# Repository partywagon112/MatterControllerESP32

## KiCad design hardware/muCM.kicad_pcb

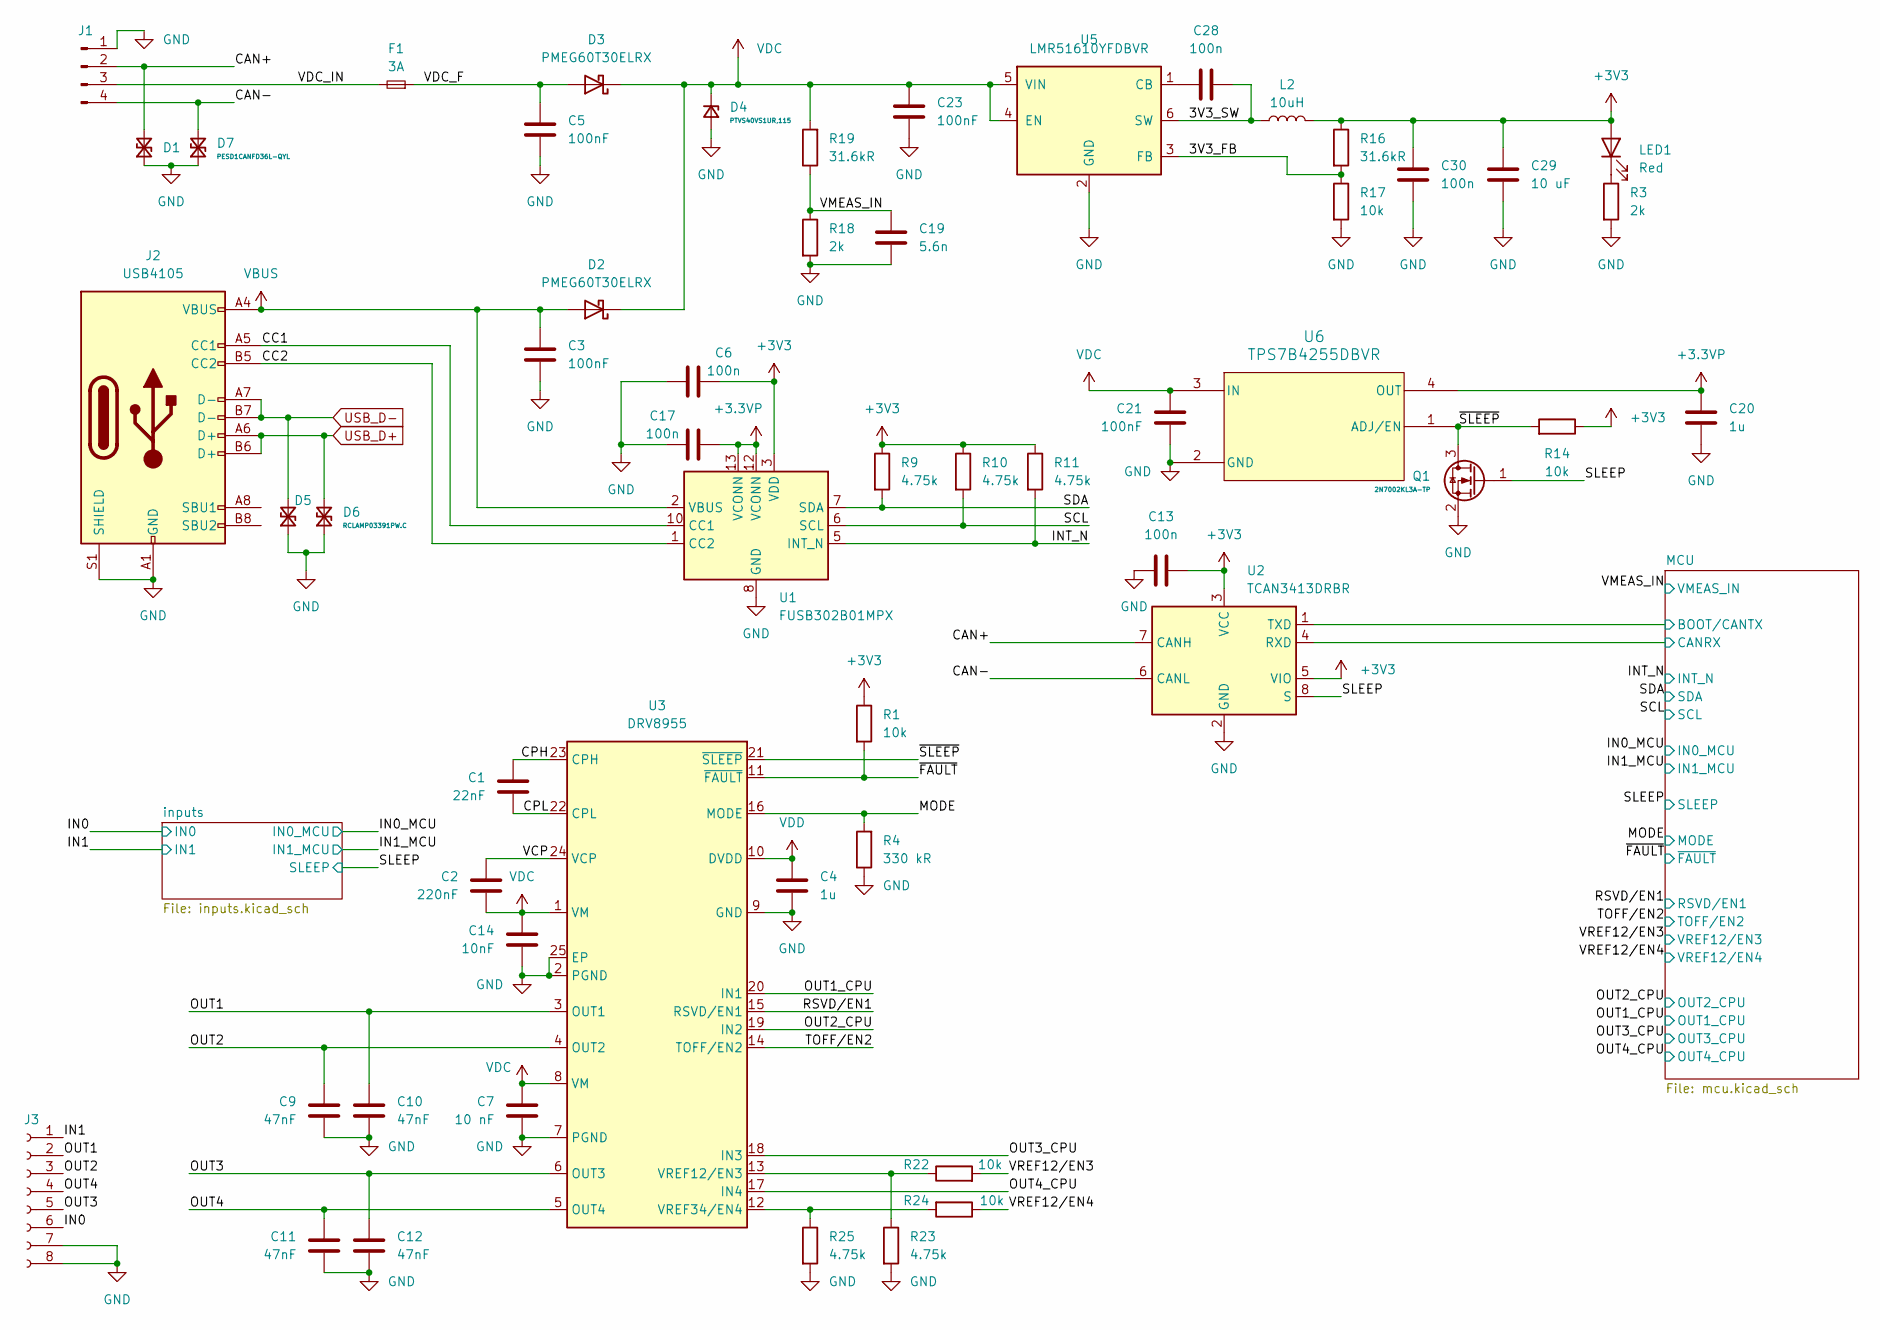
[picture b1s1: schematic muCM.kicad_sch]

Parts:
C1: 22nF; C_0603_1608Metric; MPN CL10B223KC8WPNC; DigiKey SPN 1276-CL10B223KC8WPNCCT-ND
C2: 220nF; C_0603_1608Metric; MPN HMK107C7224MAHTE; DigiKey SPN 587-5013-1-ND
C3, C5, C21, C23: 100nF; C_0603_1608Metric; MPN GCJ188R72A104KA01D; DigiKey SPN 490-13420-1-ND
C4, C20: 1u; C_0603_1608Metric; MPN GRT188R61H105KE13D; DigiKey SPN 490-12330-1-ND
C6, C13, C17, C28, C30: 100n; C_0402_1005Metric; MPN GCM155R71H104KE02J
C7: 10 nF; R_0603_1608Metric; MPN GCM188R71H103KA37D; DigiKey SPN 490-4778-1-ND
C9, C10, C11, C12: 47nF; C_0603_1608Metric; MPN CGA3E3X7S2A473K080AE; DigiKey SPN 445-173702-1-ND
C14: 10nF; C_0603_1608Metric; MPN CL10B103KC8WPNC; DigiKey SPN 1276-6556-1-ND
C19: 5.6n; C_0402_1005Metric; MPN GCM155R71H562KA55D; DigiKey SPN 490-GCM155R71H562KA55DCT-ND
C29: 10 uF; C_0603_1608Metric; MPN GRT188R61E106ME13D; DigiKey SPN 490-12323-1-ND
D1, D7: PESD1CANFD36L-QYL; D_SOD-882; MPN PESD1CANFD36L-QYL; DigiKey SPN 1727-PESD1CANFD36L-QYLCT-ND
D2, D3: PMEG60T30ELRX; Nexperia_CFP3_SOD-123W; MPN PMEG60T30ELRX; DigiKey SPN 1727-7806-1-ND
D4: PTVS40VS1UR,115; Nexperia_CFP3_SOD-123W; MPN PTVS40VS1UR,115; DigiKey SPN 1727-5873-1-ND
D5, D6: RCLAMP03391PW.C; D_SOD-882; MPN RCLAMP03391PW.C; DigiKey SPN 600-RCLAMP03391PW.CCT-ND
F1: 3A; Fuse_0805_2012Metric; MPN MFU0805FF03000P100; DigiKey SPN MFU08053.00CT-ND
J1: CDM806-04A-MP-F011-67; CUI_CDM806-04A-MP-F011-67; MPN CDM806-04A-MP-F011-67; DigiKey SPN 2223-CDM806-04A-MP-F011-67-ND
J2: USB4105; USB_C_Receptacle_GCT_USB4105-xx-A_16P_TopMnt_Horizontal; MPN USB4105-GF-A; DigiKey SPN 2073-USB4105-GF-ACT-ND
J3: CDM805-08A-FP-F011-67; CUI_CDM805-08A-FP-F011-67; MPN CDM805-08A-FP-F011-67; DigiKey SPN 2223-CDM805-08A-FP-F011-67-ND
L2: 10uH; L_1008_2520Metric; MPN SRN2510BTA-100M; DigiKey SPN 118-SRN2510BTA-100MCT-ND
LED1: Red; LED_0603_1608Metric; MPN 150060SS75020
Q1: 2N7002KL3A-TP; Diodes_DFN1006-3; MPN 2N7002KL3A-TP; DigiKey SPN 353-2N7002KL3A-TPCT-ND
R1, R14, R17, R22, R24: 10k; R_0402_1005Metric; MPN CR0402AFX-1002GAS; DigiKey SPN CR0402AFX-1002GASCT-ND
R3, R18: 2k; R_0402_1005Metric; MPN CR0402AFX-2001GAS
R4: 330 kR; R_0402_1005Metric; MPN CRGCQ0402F330K; DigiKey SPN A129657CT-ND
R9, R10, R11, R23, R25: 4.75k; R_0402_1005Metric; MPN CR0402AFX-4751GAS; DigiKey SPN CR0402AFX-4751GASCT-ND
R16, R19: 31.6kR; R_0402_1005Metric; MPN CRCW040231K6FKED; DigiKey SPN 541-31.6KLCT-ND
U1: FUSB302B01MPX; WQFN-14-1EP_2.5x2.5mm_P0.5mm_EP1.45x1.45mm; MPN FUSB302B01MPX; DigiKey SPN FUSB302B01MPXCT-ND
U2: TCAN3413DRBR; VSON-8-1EP_3x3mm_P0.65mm_EP1.6x2.4mm; MPN TCAN3413DRBR; DigiKey SPN 296-TCAN3413DRBRCT-ND
U3: DRV8955; VQFN-24-1EP_4x4mm_P0.5mm_EP2.45x2.45mm; MPN DRV8955PRGER; DigiKey SPN 296-DRV8955PRGERCT-ND
U5: LMR51610YFDBVR; SOT-23-6; MPN LMR51610YFDBVR; DigiKey SPN 296-LMR51610YFDBVRCT-ND
U6: TPS7B4255DBVR; SOT-23-5; MPN TPS7B4255DBVR; DigiKey SPN 296-TPS7B4255DBVRCT-ND

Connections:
+3.3VP: C17.1, C20.1, U1.12 (VCONN), U1.13 (VCONN), U6.4 (OUT); also elsewhere on the board
+3V3: C6.1, C13.2, C29.1, C30.1, L2.2, LED1.2 (A), R1.1, R9.1, R10.1, R11.1, R14.1, R16.1, U1.3 (VDD), U1.4 (VDD), U2.3 (VCC), U2.5 (VIO); also elsewhere on the board
/3V3_FB: R16.2, R17.1, U5.3 (FB)
/3V3_SW: C28.2, L2.1, U5.6 (SW)
/CAN+: D1.2 (A2), J1.2, U2.7 (CANH)
/CAN-: D7.2 (A2), J1.4, U2.6 (CANL)
/CC1: J2.A5 (CC1), U1.10 (CC1), U1.11 (CC1)
/CC2: J2.B5 (CC2), U1.1 (CC2), U1.14 (CC2)
/CPH: C1.1, U3.23 (CPH)
/CPL: C1.2, U3.22 (CPL)
/IN0: J3.6; also elsewhere on the board
/IN1: J3.1; also elsewhere on the board
/INT_N: R11.2, U1.5 (INT_N); also elsewhere on the board
/MCU/BOOT/CANTX: U2.1 (TXD); also elsewhere on the board
/MCU/CANRX: U2.4 (RXD); also elsewhere on the board
/MODE: R4.2, U3.16 (MODE); also elsewhere on the board
/OUT1: C10.1, J3.2, U3.3 (OUT1)
/OUT1_CPU: U3.20 (IN1); also elsewhere on the board
/OUT2: C9.1, J3.3, U3.4 (OUT2)
/OUT2_CPU: U3.19 (IN2); also elsewhere on the board
/OUT3: C12.1, J3.5, U3.6 (OUT3)
/OUT3_CPU: U3.18 (IN3); also elsewhere on the board
/OUT4: C11.1, J3.4, U3.5 (OUT4)
/OUT4_CPU: U3.17 (IN4); also elsewhere on the board
/RSVD/EN1: U3.15 (RSVD/EN1); also elsewhere on the board
/SCL: R10.2, U1.6 (SCL); also elsewhere on the board
/SDA: R9.2, U1.7 (SDA); also elsewhere on the board
/SLEEP: Q1.1 (G), U2.8 (S); also elsewhere on the board
/TOFF/EN2: U3.14 (TOFF/EN2); also elsewhere on the board
/VCP: C2.1, U3.24 (VCP)
/VDC_F: C5.1, D3.2 (A), F1.1
/VDC_IN: F1.2, J1.3
/VMEAS_IN: C19.1, R18.1, R19.1; also elsewhere on the board
/VREF12/EN3: R22.2; also elsewhere on the board
/VREF12/EN4: R24.1; also elsewhere on the board
/~FAULT: R1.2, U3.11 (~FAULT); also elsewhere on the board
/~SLEEP: Q1.3 (D), R14.2, U3.21 (~SLEEP), U6.1 (ADJ/EN)
GND: C3.2, C4.2, C5.2, C6.2, C7.2, C9.2, C10.2, C11.2, C12.2, C13.1, C14.2, C17.2, C19.2, C20.2, C21.2, C23.2, C29.2, C30.2, D1.1 (A1), D4.2 (A), D5.1 (A1), D6.1 (A1), D7.1 (A1), J1.1, J2.A1 (GND), J2.A12 (GND), J2.B1 (GND), J2.B12 (GND), J2.S1 (SHIELD), J3.7, J3.8, Q1.2 (S), R3.2, R4.1, R17.2, R18.2, R23.2, R25.2, U1.8 (GND), U1.9 (GND), U1.15 (GND), U2.2 (GND), U2.9, U3.2 (PGND), U3.7 (PGND), U3.9 (GND), U3.25 (EP), U5.2 (GND), U6.2 (GND); also elsewhere on the board
unnamed: LED1.1 (K), R3.1
unnamed: R22.1, R23.1, U3.13 (VREF12/EN3)
unnamed: R24.2, R25.1, U3.12 (VREF34/EN4)
unnamed: C28.1, U5.1 (CB)
USB_D+: D6.2 (A2), J2.A6 (D+), J2.B6 (D+); also elsewhere on the board
USB_D-: D5.2 (A2), J2.A7 (D-), J2.B7 (D-); also elsewhere on the board
VBUS: C3.1, D2.2 (A), J2.A4 (VBUS), J2.A9 (VBUS), J2.B4 (VBUS), J2.B9 (VBUS), U1.2 (VBUS)
VDC: C2.2, C7.1, C14.1, C21.1, C23.1, D2.1 (K), D3.1 (K), D4.1 (K), R19.2, U3.1 (VM), U3.8 (VM), U5.4 (EN), U5.5 (VIN), U6.3 (IN)
VDD: C4.1, U3.10 (DVDD)

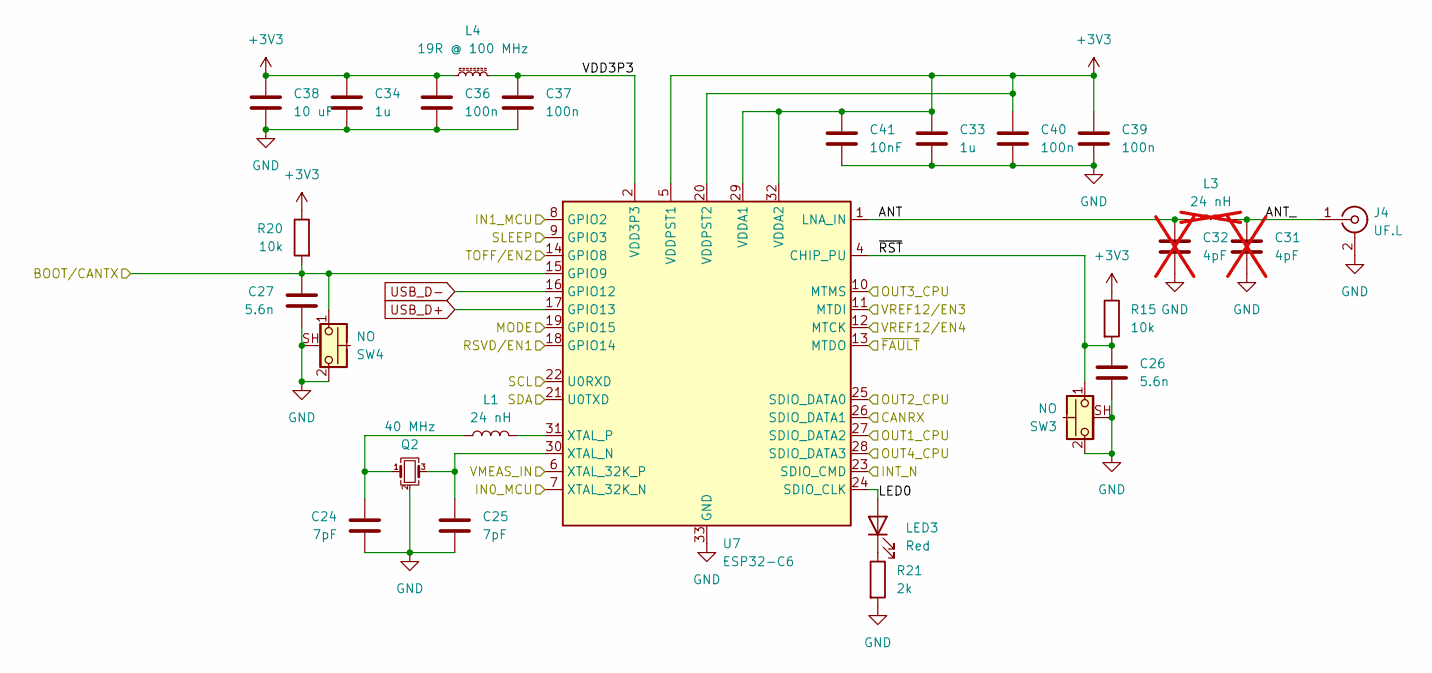
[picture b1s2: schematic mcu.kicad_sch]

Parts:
C24, C25: 7pF; C_0402_1005Metric; MPN GCM1555C1H7R0BA16D; DigiKey SPN 490-GCM1555C1H7R0BA16DCT-ND
C26, C27: 5.6n; C_0402_1005Metric; MPN GCM155R71H562KA55D; DigiKey SPN 490-GCM155R71H562KA55DCT-ND
C31, C32: 4pF; C_0402_1005Metric; MPN GCM1555C1H4R0BA16D; DigiKey SPN 490-GCM1555C1H4R0BA16DCT-ND; not fitted
C33, C34: 1u; C_0603_1608Metric; MPN GRT188R61H105KE13D; DigiKey SPN 490-12330-1-ND
C36, C37, C39, C40: 100n; C_0402_1005Metric; MPN GCM155R71H104KE02J
C38: 10 uF; C_0603_1608Metric; MPN GRT188R61E106ME13D; DigiKey SPN 490-12323-1-ND
C41: 10nF; C_0402_1005Metric; MPN GCM155R71H103KA55D; DigiKey SPN 490-4762-1-ND
J4: UF.L; U.FL_Hirose_U.FL-R-SMT-1_Vertical; MPN U.FL-R-SMT(10); DigiKey SPN H9161CT-ND
L1: 24 nH; L_0402_1005Metric; MPN MLG1005S24NJTD25; DigiKey SPN 445-16275-1-ND
L3: 24 nH; L_0402_1005Metric; MPN MLG1005S24NJTD25; DigiKey SPN 445-16275-1-ND; not fitted
L4: 19R @ 100 MHz; L_0402_1005Metric; MPN LI0402E190R-10; DigiKey SPN 240-LI0402E190R-10CT-ND
LED3: Red; LED_0603_1608Metric; MPN 150060SS75020
Q2: 40 MHz; Crystal_SMD_2016-4Pin_2.0x1.6mm; MPN XTL501100-M118-207; DigiKey SPN 3994-XTL501100-M118-207CT-ND
R15, R20: 10k; R_0402_1005Metric; MPN CR0402AFX-1002GAS; DigiKey SPN CR0402AFX-1002GASCT-ND
R21: 2k; R_0402_1005Metric; MPN CR0402AFX-2001GAS
SW3, SW4: NO; SW_Push_1P1T-SH_NO_CK_KMR2xxG; MPN KMR221G LFS; DigiKey SPN 401-1427-1-ND
U7: ESP32-C6; QFN-32-1EP_5x5mm_P0.5mm_EP3.7x3.7mm; MPN ESP32-C6FH4; DigiKey SPN 1904-ESP32-C6FH4CT-ND

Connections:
+3V3: C33.1, C34.1, C36.1, C38.1, C39.1, C40.1, C41.1, L4.1, R15.1, R20.1, U7.5 (VDDPST1), U7.20 (VDDPST2), U7.29 (VDDA1), U7.32 (VDDA2); also elsewhere on the board
/IN0_MCU: U7.7 (XTAL_32K_N); also elsewhere on the board
/IN1_MCU: U7.8 (GPIO2); also elsewhere on the board
/INT_N: U7.23 (SDIO_CMD); also elsewhere on the board
/MCU/ANT: C32.1, L3.1, U7.1 (LNA_IN)
/MCU/ANT_: C31.1, J4.1 (In), L3.2
/MCU/BOOT/CANTX: C27.1, R20.2, SW4.1, U7.15 (GPIO9); also elsewhere on the board
/MCU/CANRX: U7.26 (SDIO_DATA1); also elsewhere on the board
/MCU/LED0: LED3.2 (A), U7.24 (SDIO_CLK)
/MCU/~RST: C26.1, R15.2, SW3.1, U7.4 (CHIP_PU)
/MODE: U7.19 (GPIO15); also elsewhere on the board
/OUT1_CPU: U7.27 (SDIO_DATA2); also elsewhere on the board
/OUT2_CPU: U7.25 (SDIO_DATA0); also elsewhere on the board
/OUT3_CPU: U7.10 (MTMS); also elsewhere on the board
/OUT4_CPU: U7.28 (SDIO_DATA3); also elsewhere on the board
/RSVD/EN1: U7.18 (GPIO14); also elsewhere on the board
/SCL: U7.22 (U0RXD); also elsewhere on the board
/SDA: U7.21 (U0TXD); also elsewhere on the board
/SLEEP: U7.9 (GPIO3); also elsewhere on the board
/TOFF/EN2: U7.14 (GPIO8); also elsewhere on the board
/VMEAS_IN: U7.6 (XTAL_32K_P); also elsewhere on the board
/VREF12/EN3: U7.11 (MTDI); also elsewhere on the board
/VREF12/EN4: U7.12 (MTCK); also elsewhere on the board
/~FAULT: U7.13 (MTDO); also elsewhere on the board
GND: C24.2, C25.2, C26.2, C27.2, C31.2, C32.2, C33.2, C34.2, C36.2, C37.2, C38.2, C39.2, C40.2, C41.2, J4.2 (Ext), Q2.2 (G), Q2.4 (G), R21.2, SW3.2, SW3.SH (B), SW4.2, SW4.SH (B), U7.33 (GND); also elsewhere on the board
unnamed: C24.1, L1.1, Q2.1
unnamed: LED3.1 (K), R21.1
unnamed: C25.1, Q2.3, U7.30 (XTAL_N)
unnamed: L1.2, U7.31 (XTAL_P)
USB_D+: U7.17 (GPIO13); also elsewhere on the board
USB_D-: U7.16 (GPIO12); also elsewhere on the board
VDD3P3: C37.1, L4.2, U7.2 (VDD3P3), U7.3 (VDD3P3)

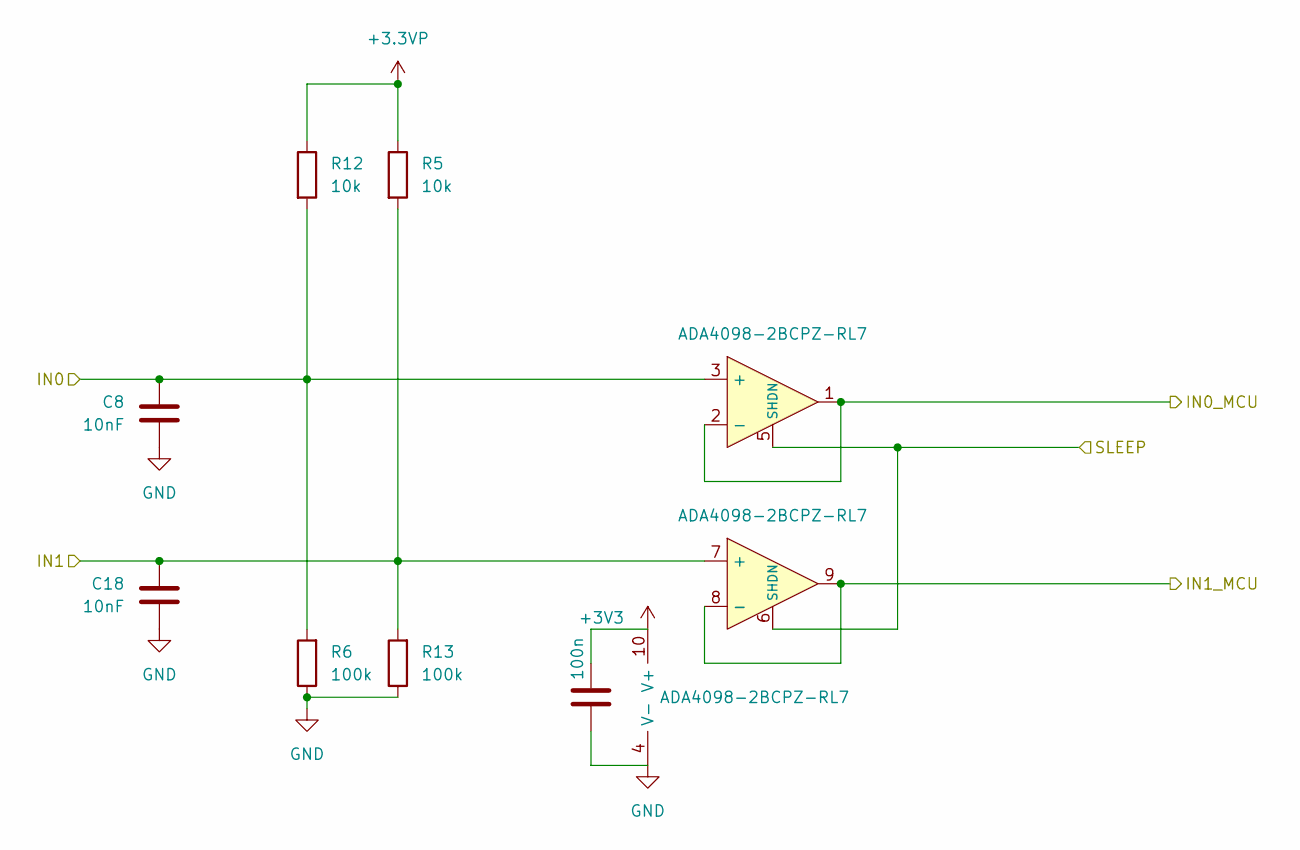
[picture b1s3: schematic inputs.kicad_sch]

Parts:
C8, C18: 10nF; C_0603_1608Metric; MPN CL10B103KC8WPNC; DigiKey SPN 1276-6556-1-ND
C22: 100n; C_0402_1005Metric; MPN GCM155R71H104KE02J
R5, R12: 10k; R_0402_1005Metric; MPN CR0402AFX-1002GAS; DigiKey SPN CR0402AFX-1002GASCT-ND
R6, R13: 100k; R_0402_1005Metric; MPN ERJ-2RKF1003X; DigiKey SPN P100KLCT-ND
U4: ADA4098-2BCPZ-RL7; LFCSP-WD-10-1EP_3x3mm_P0.5mm_EP1.64x2.38mm; MPN ADA4098-2BCPZ-RL7; DigiKey SPN 505-ADA4098-2BCPZ-RL7TR-ND

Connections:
+3.3VP: R5.1, R12.1; also elsewhere on the board
+3V3: C22.1, U4.10 (V+); also elsewhere on the board
/IN0: C8.1, R6.2, R12.2, U4.3 (+); also elsewhere on the board
/IN0_MCU: U4.1, U4.2 (-); also elsewhere on the board
/IN1: C18.1, R5.2, R13.2, U4.7 (+); also elsewhere on the board
/IN1_MCU: U4.8 (-), U4.9; also elsewhere on the board
/SLEEP: U4.5 (SHDN), U4.6 (SHDN); also elsewhere on the board
GND: C8.2, C18.2, C22.2, R6.1, R13.1, U4.4 (V-), U4.11 (V-); also elsewhere on the board

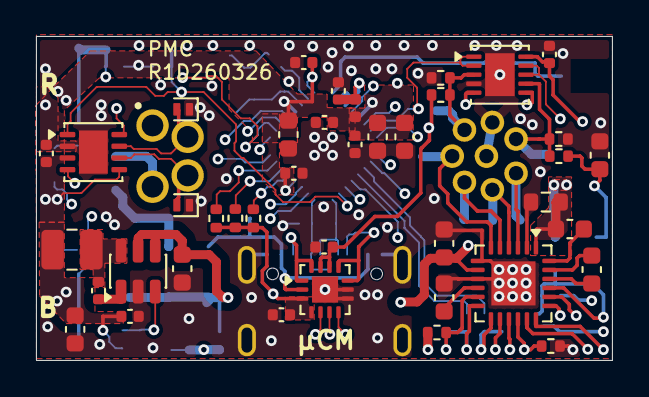
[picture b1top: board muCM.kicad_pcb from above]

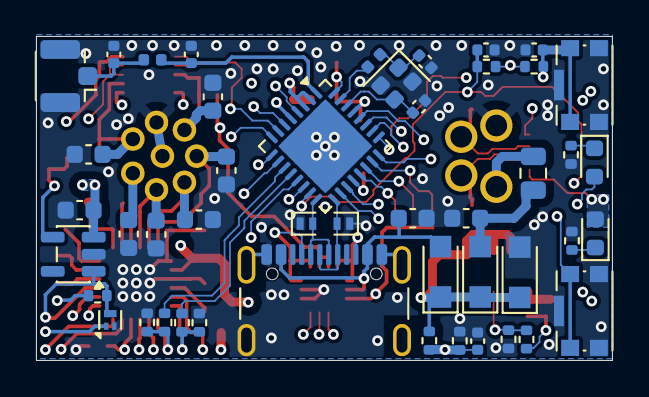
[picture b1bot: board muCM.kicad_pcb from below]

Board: 4 copper layers, 32.0 x 18.0 mm, 89 parts (47 on the bottom side), 58 nets.

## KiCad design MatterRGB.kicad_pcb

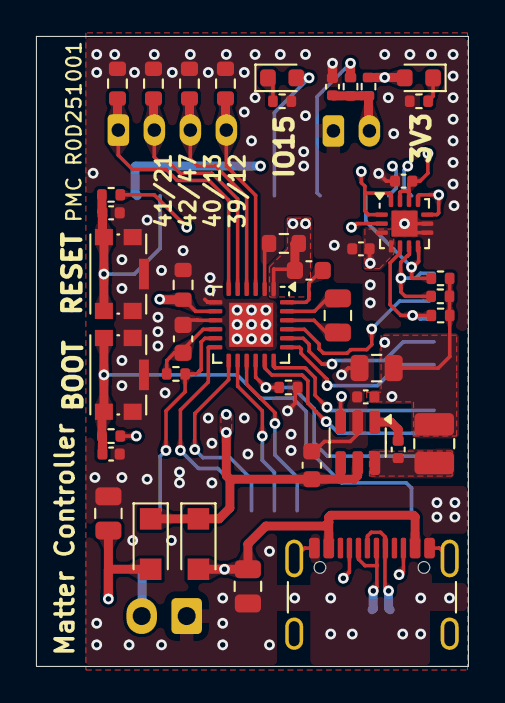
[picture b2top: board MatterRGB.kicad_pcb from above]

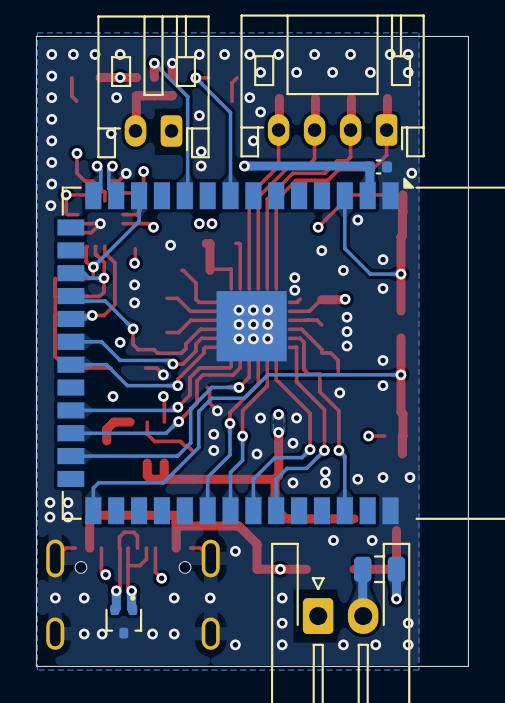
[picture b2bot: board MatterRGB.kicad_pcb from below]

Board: 4 copper layers, 24.0 x 35.0 mm, 49 parts (7 on the bottom side), 41 nets.

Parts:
C1: 22nF; C_0805_2012Metric
C2, C31: 220nF; C_0603_1608Metric
C3, C5: 100n; C_0805_2012Metric
C4: 1u; C_0603_1608Metric
C6, C8, C13, C17, C28, C30: 100n; C_0402_1005Metric
C7, C9, C10, C11, C12, C14: 10 nF; R_0603_1608Metric
C15, C16: 5.6n; C_0402_1005Metric
C29: 10uF; C_0805_2012Metric
D1: RCLAMP0582B.TCT; SOT-416
D2, D3: PMEG60T30ELRX; Nexperia_CFP3_SOD-123W
F1: 5A; Fuse_0805_2012Metric
J1: USB4105; USB_C_Receptacle_GCT_USB4105-xx-A_16P_TopMnt_Horizontal
J2: S4B-PH-K-S; JST_PH_S4B-PH-K_1x04_P2.00mm_Horizontal
J4: S2B-XH-A-1; JST_XH_S2B-XH-A-1_1x02_P2.50mm_Horizontal
J5: S2B-PH-K-S; JST_PH_S2B-PH-K_1x02_P2.00mm_Horizontal
L2: 6.8 uH; L_1008_2520Metric
LED1, LED2: Red; LED_0603_1608Metric
R1, R5, R6, R7, R8: 10k; R_0402_1005Metric
R2, R3: 2k; R_0402_1005Metric
R4: 330 kR; R_0402_1005Metric
R9, R10, R11: 4.75k; R_0402_1005Metric
SW1, SW2: NO; SW_Push_1P1T-SH_NO_CK_KMR2xxG
U1: FUSB302B01MPX; WQFN-14-1EP_2.5x2.5mm_P0.5mm_EP1.45x1.45mm
U2: ESP32-S3-WROOM-1-N8R8; ESP32-S3-WROOM-1
U3: DRV8955; VQFN-24-1EP_4x4mm_P0.5mm_EP2.45x2.45mm
U5: LMR50410Y3FQDBVRQ1; SOT-23-6

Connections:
+3V3: C6.1, C13.1, C17.1, C29.1, C30.1, L2.2, LED1.2 (A), R5.1, R7.1, R8.1, R9.1, R10.1, R11.1, U1.3 (VDD), U1.4 (VDD), U1.12 (VCONN), U1.13 (VCONN), U2.2 (3V3), U5.3 (FB)
/3V3_SW: C28.2, L2.1, U5.6 (SW)
/BOOT: C16.1, R8.2, SW2.2, U2.27 (IO0)
/CC1: J1.A5 (CC1), U1.10 (CC1), U1.11 (CC1)
/CC2: J1.B5 (CC2), U1.1 (CC2), U1.14 (CC2)
/CPH: C1.1, U3.23 (CPH)
/CPL: C1.2, U3.22 (CPL)
/IN0: R6.2, U2.10 (IO17)
/IN1: U2.20 (IO12), U3.20 (IN1)
/IN2: U2.21 (IO13), U3.19 (IN2)
/IN3: U2.23 (IO21), U3.18 (IN3)
/IN4: U2.24 (IO47), U3.17 (IN4)
/INT_N: R11.2, U1.5 (INT_N), U2.19 (IO11)
/MODE: R4.2, U2.25 (IO48), U3.16 (MODE)
/OUT1: C9.1, J2.4, U3.3 (OUT1)
/OUT2: C10.1, J2.3, U3.4 (OUT2)
/OUT3: C11.1, J2.1, U3.6 (OUT3)
/OUT4: C12.1, J2.2, U3.5 (OUT4)
/RESET: C15.1, R7.2, SW1.2, U2.3 (EN)
/RSVD/EN1: U2.32 (IO39), U3.15 (RSVD/EN1)
/SCL: R10.2, U1.6 (SCL), U2.17 (IO9)
/SDA: R9.2, U1.7 (SDA), U2.12 (IO8)
/TOFF/EN2: U2.33 (IO40), U3.14 (TOFF/EN2)
/VCP: C2.1, U3.24 (VCP)
/VREF12/EN3: U2.34 (IO41), U3.13 (VREF12/EN3)
/VREF12/EN4: U2.35 (IO42), U3.12 (VREF12/EN4)
/~FAULT: R1.2, U2.38 (IO2), U3.11 (~FAULT)
/~SLEEP: U2.18 (IO10), U3.21 (~SLEEP)
GND: C3.2, C4.2, C5.2, C6.2, C7.2, C8.2, C9.2, C10.2, C11.2, C12.2, C13.2, C14.2, C15.2, C16.2, C17.2, C29.2, C30.2, C31.2, D1.3 (A), J1.A1 (GND), J1.A12 (GND), J1.B1 (GND), J1.B12 (GND), J1.S1 (SHIELD), J4.1, J5.1, R2.2, R3.2, R4.1, SW1.1, SW1.SH (B), SW2.1, SW2.SH (B), U1.8 (GND), U1.9 (GND), U1.15 (GND), U2.1 (GND), U2.40 (GND), U2.41 (GND), U3.2 (PGND), U3.7 (PGND), U3.9 (GND), U3.25 (EP), U5.2 (GND)
unnamed: C5.1, D3.2 (A), F1.1
unnamed: F1.2, J4.2
unnamed: C8.1, J5.2, R5.2, R6.1
unnamed: LED1.1 (K), R3.1
unnamed: LED2.2 (A), U2.8 (IO15)
unnamed: LED2.1 (K), R2.1
unnamed: C28.1, U5.1 (CB)
USB_D+: D1.2 (K2), J1.A6 (D+), J1.B6 (D+), U2.14 (USB_D+)
USB_D-: D1.1 (K1), J1.A7 (D-), J1.B7 (D-), U2.13 (USB_D-)
VBUS: C3.1, D2.2 (A), J1.A4 (VBUS), J1.A9 (VBUS), J1.B4 (VBUS), J1.B9 (VBUS), U1.2 (VBUS)
VDC: C2.2, C7.1, C14.1, C31.1, D2.1 (K), D3.1 (K), U3.1 (VM), U3.8 (VM), U5.4 (EN), U5.5 (VIN)
VDD: C4.1, R1.1, U3.10 (DVDD)

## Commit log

2026-03-25 removing zips from upload
2026-03-25 finished single board layout - upping to panel size
2026-06-24 Added stencils and other stuff i guess - should commit more regularly
2026-06-24 yeah, i'm not bothering to clen this
